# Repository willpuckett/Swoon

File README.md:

# Swoon Half Xiao'd

> Yet another diode matrix rework of the
> [Ferris Sweep Half Swept](https://github.com/davidphilipbarr/Sweep/tree/main/Sweep%20half-swept)
> for
> [Seeed Xiao nRF52840](https://www.seeedstudio.com/Seeed-XIAO-BLE-nRF52840-p-5201.html).

## Motivations

- Utilise Seeed Xiao—it's cuter
- Experiment with parts consignment for PCBA of hotswaps
- Choose a battery that can be easily changed by users who do not solder
  (LIR1254)
- Explore using CI/CD for board variants, case, and top plate generation
- Locate each half's components on its respective top side for more affordable
  assembly and lower overall height

> [!NOTE]
> In a Hurry? Here are the relevant links for download. No need scroll...
>
> Boards [[flip](/jlcpcb/swoon_FLIP.zip)] [[left](/jlcpcb/swoon_LEFT.zip)]
> [[right](/jlcpcb/swoon_RIGHT.zip)] [[both](/jlcpcb/swoon_BOTH.zip)]
>
> Case
> [[step](https://nightly.link/willpuckett/Swoon/actions/runs/10987780383/Case_STEP.zip)]
> [[stl](https://nightly.link/willpuckett/Swoon/actions/runs/10987780383/Case_STL.zip)]
>
> Firmware
> [[latest ZMK Builds](https://nightly.link/willpuckett/Swoon/workflows/zmk/main/swoon.zip)]

## Variants

[^1]

### **Flip**

> [!IMPORTANT]
> You'll need to solder the upward facing jumpers on each half under the Xiao
> before use.

A flippable variant [[flip](/jlcpcb/swoon_FLIP.zip)] for hand-soldering, like
the original half-swept. **Flip** is also the most cost conscious variant—about
$7.60 to get 5 of the boards produced, enough for 2 full keyboads and a nice...
coaster?

> [!CAUTION]
> Use 3.7v LIR1254 (lithium ion rechargable) battery **only**.

#### BOM

|      QTY      |                   Part                    | JLCPCB Part # |
| :-----------: | :---------------------------------------: | :-----------: |
|       2       |          0906-2-15-20-75-14-11-0          |   C5261048    |
|       2       |            BAT-SMD_MY-LR44-02             |   C2902345    |
|       4       | 310-13-107-41-001000 or MF254V-11-07-0743 |   C5504401    |
| 68 (optional) |          3305-0-15-80-47-27-10-0          |   C17370797   |
|       2       |               MST22D18G2125               |   C2906280    |
|      34       | CD4148WS (or 1N4148 SOD-323 from Amazon)  |   C38587762   |
|      34       |      Your ChocV1 switches of choice       |      N/A      |
|       2       |         3.7V LIR1254 (NOT LR44!)          |      N/A      |

### **Left** and **Right**

These variants are designed to be produced and assembled by JLCPCB. Each zip
file [[left](/jlcpcb/swoon_LEFT.zip)] [[right](/jlcpcb/swoon_RIGHT.zip)] has the
a gerbers/drill zip, a cpl, and bom file. They should be fully assemblable, but
you'll need to preorder the parts through global sourcing before paying. The
3305s aren't cheap and they cost extra to assemble.

Each half is pre-jumpered in the gerbers so you can print and go.

> [!CAUTION]
> Use 3.7v LIR1254 (lithium ion rechargable) battery **only**.

There's also a [[both](/jlcpcb/swoon_BOTH.zip)] that will probably supersede the
**left** and **right** since it's cheaper to produce as a single piece.

## Case

There's a case
[[step](https://nightly.link/willpuckett/Swoon/actions/runs/10987780383/Case_STEP.zip)]
[[stl](https://nightly.link/willpuckett/Swoon/actions/runs/10987780383/Case_STL.zip)]
that's really more of a skin. Print and place the pcb directly in it.

> [!TIP]
> Polymaker TPU works well. It seems to like to print slow and cool—leave the
> door open.

TPU is relatively non-slip, and it absorbs and distributes the force of typing
very nicely, so no bumpons needed which further reduces height.

## Layouts

Download the
[latest ZMK Builds](https://nightly.link/willpuckett/Swoon/workflows/zmk/main/swoon.zip).
The link contains the following layouts...

### QWERTY

### Engram

### Engrammer

[^1]: This project is mostly setup for production and assembly variants in
    GitHub actions. ~~Production variants are newer to KiCad and there's still a
    few kinks, but hopefully they'll be worked out soon.~~ The KiBot team has
    resolved the issues this project will pull them in for a release shortly. In
    the mean time, use the files in the [jlcpcb](/jlcpcb/) directory.

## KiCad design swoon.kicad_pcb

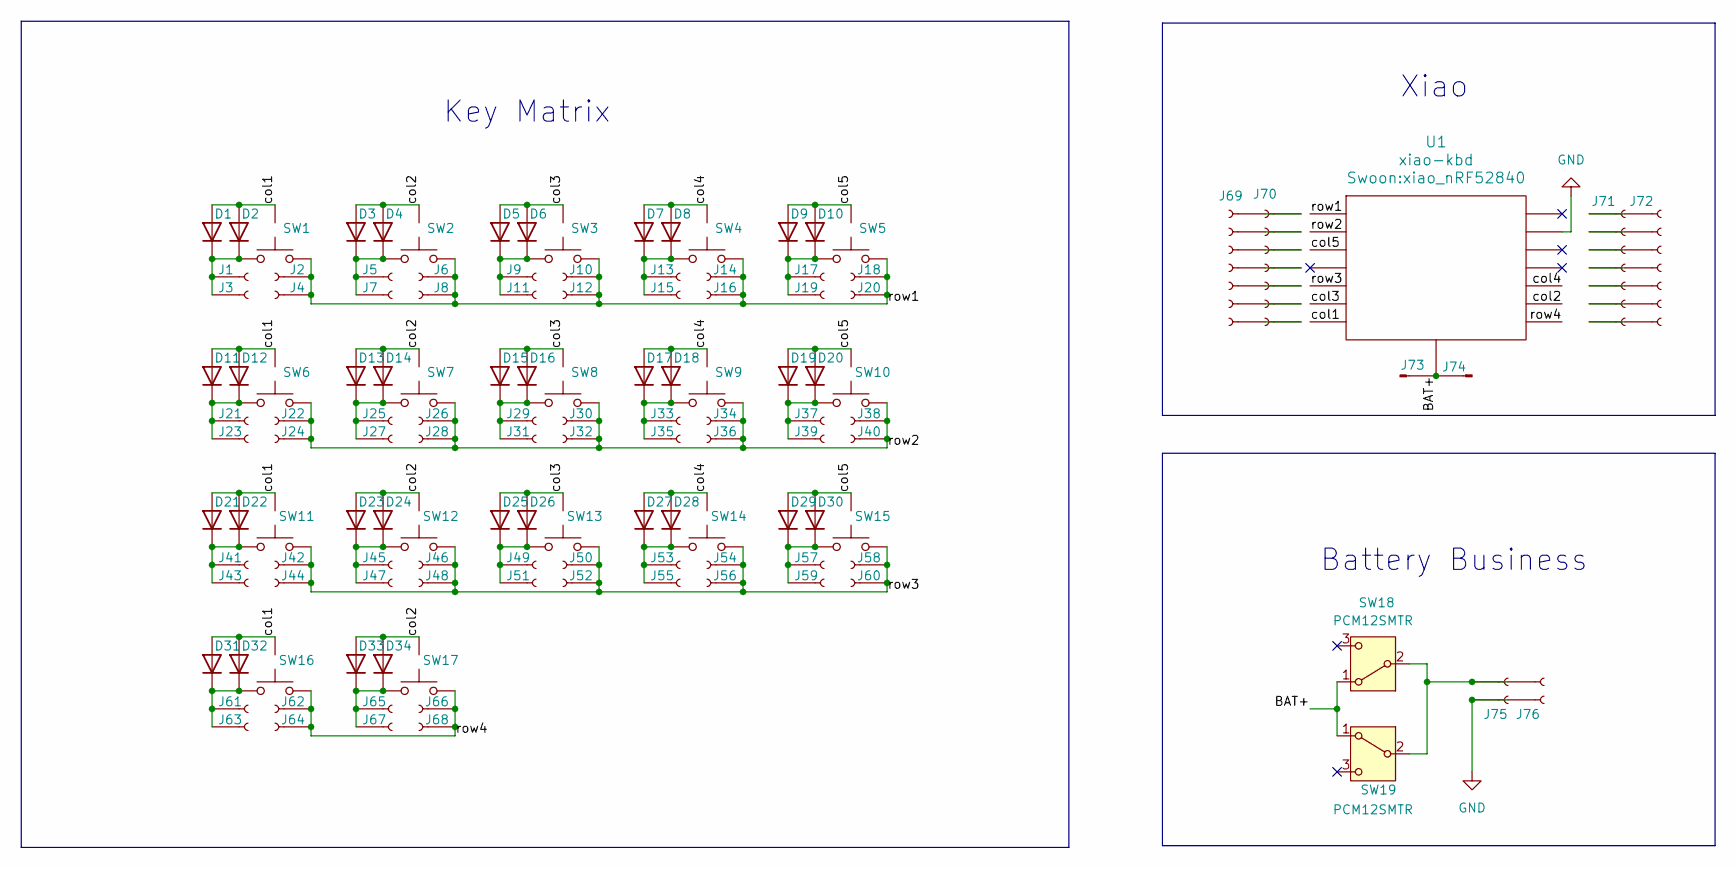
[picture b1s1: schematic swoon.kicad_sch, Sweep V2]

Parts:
D1, D2, D3, D4, D5, D6, D7, D8, D9, D10, D11, D12, D13, D14, D15, D16, D17, D18, D19, D20, D21, D22, D23, D24, D25, D26, D27, D28, D29, D30, D31, D32, D33, D34: CD4148WSP-C109001; D_0805_2012Metric
J1, J2, J3, J4, J5, J6, J7, J8, J9, J10, J11, J12, J13, J14, J15, J16, J17, J18, J19, J20, J21, J22, J23, J24, J25, J26, J27, J28, J29, J30, J31, J32, J33, J34, J35, J36, J37, J38, J39, J40, J41, J42, J43, J44, J45, J46, J47, J48, J49, J50, J51, J52, J53, J54, J55, J56, J57, J58, J59, J60, J61, J62, J63, J64, J65, J66, J67, J68: 3305-0-15-80-47-27-10-0
J69, J70, J71, J72: MF254V-11-07-0743
J73, J74: Mill Max 0906-2-15-20-75-14-11-0; 0906-2-15-20-75-14-11-0
J75, J76: JST SM02B-SRSS-TB(LF)(SN); JST_SH_SM02B-SRSS-TB_1x02-1MP_P1.00mm_Horizontal
SW1, SW2, SW3, SW4, SW5, SW6, SW7, SW8, SW9, SW10, SW11, SW12, SW13, SW14, SW15, SW16, SW17: SW_Push; SW_PG1350_vias
SW18, SW19: PCM12SMTR; SW_PCM12SMTR
U1: xiao-kbd; xiao_nRF52840

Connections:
/BAT+: J73.1, J74.1, SW18.1 (A), SW19.1 (A), U1.15 (BAT+)
/col1: D1.2 (A), D2.2 (A), D11.2 (A), D12.2 (A), D21.2 (A), D22.2 (A), D31.2 (A), D32.2 (A), SW1.3, SW6.3, SW11.3, SW16.3, U1.7 (D6)
/col2: D3.2 (A), D4.2 (A), D13.2 (A), D14.2 (A), D23.2 (A), D24.2 (A), D33.2 (A), D34.2 (A), SW2.3, SW7.3, SW12.3, SW17.3, U1.9 (D8)
/col3: D5.2 (A), D6.2 (A), D15.2 (A), D16.2 (A), D25.2 (A), D26.2 (A), SW3.3, SW8.3, SW13.3, U1.6 (D5)
/col4: D7.2 (A), D8.2 (A), D17.2 (A), D18.2 (A), D27.2 (A), D28.2 (A), SW4.3, SW9.3, SW14.3, U1.10 (D9)
/col5: D9.2 (A), D10.2 (A), D19.2 (A), D20.2 (A), D29.2 (A), D30.2 (A), SW5.3, SW10.3, SW15.3, U1.3 (D2)
/row1: J2.1, J4.1, J6.1, J8.1, J10.1, J12.1, J14.1, J16.1, J18.1, J20.1, SW1.1, SW2.1, SW3.1, SW4.1, SW5.1, U1.1 (D0)
/row2: J22.1, J24.1, J26.1, J28.1, J30.1, J32.1, J34.1, J36.1, J38.1, J40.1, SW6.1, SW7.1, SW8.1, SW9.1, SW10.1, U1.2 (D1)
/row3: J42.1, J44.1, J46.1, J48.1, J50.1, J52.1, J54.1, J56.1, J58.1, J60.1, SW11.1, SW12.1, SW13.1, SW14.1, SW15.1, U1.5 (D4)
/row4: J62.1, J64.1, J66.1, J68.1, SW16.1, SW17.1, U1.8 (D7)
GND: J75.1, J76.1, U1.13 (GND)
unnamed: D1.1 (K), D2.1 (K), J1.1, J3.1, SW1.2
unnamed: D3.1 (K), D4.1 (K), J5.1, J7.1, SW2.2
unnamed: D5.1 (K), D6.1 (K), J9.1, J11.1, SW3.2
unnamed: D7.1 (K), D8.1 (K), J13.1, J15.1, SW4.2
unnamed: D9.1 (K), D10.1 (K), J17.1, J19.1, SW5.2
unnamed: D11.1 (K), D12.1 (K), J21.1, J23.1, SW6.2
unnamed: D13.1 (K), D14.1 (K), J25.1, J27.1, SW7.2
unnamed: D15.1 (K), D16.1 (K), J29.1, J31.1, SW8.2
unnamed: D17.1 (K), D18.1 (K), J33.1, J35.1, SW9.2
unnamed: D19.1 (K), D20.1 (K), J37.1, J39.1, SW10.2
unnamed: D21.1 (K), D22.1 (K), J41.1, J43.1, SW11.2
unnamed: D23.1 (K), D24.1 (K), J45.1, J47.1, SW12.2
unnamed: D25.1 (K), D26.1 (K), J49.1, J51.1, SW13.2
unnamed: D27.1 (K), D28.1 (K), J53.1, J55.1, SW14.2
unnamed: D29.1 (K), D30.1 (K), J57.1, J59.1, SW15.2
unnamed: D31.1 (K), D32.1 (K), J61.1, J63.1, SW16.2
unnamed: D33.1 (K), D34.1 (K), J65.1, J67.1, SW17.2
unnamed: J69.1, J70.1
unnamed: J69.2, J70.2
unnamed: J69.3, J70.3
unnamed: J69.4, J70.4
unnamed: J69.5, J70.5
unnamed: J69.6, J70.6
unnamed: J69.7, J70.7
unnamed: J71.1, J72.1
unnamed: J71.2, J72.2
unnamed: J71.3, J72.3
unnamed: J71.4, J72.4
unnamed: J71.5, J72.5
unnamed: J71.6, J72.6
unnamed: J71.7, J72.7
unnamed: J75.2, J76.2, SW18.2 (B), SW19.2 (B)

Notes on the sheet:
Battery Business
Key Matrix
Xiao

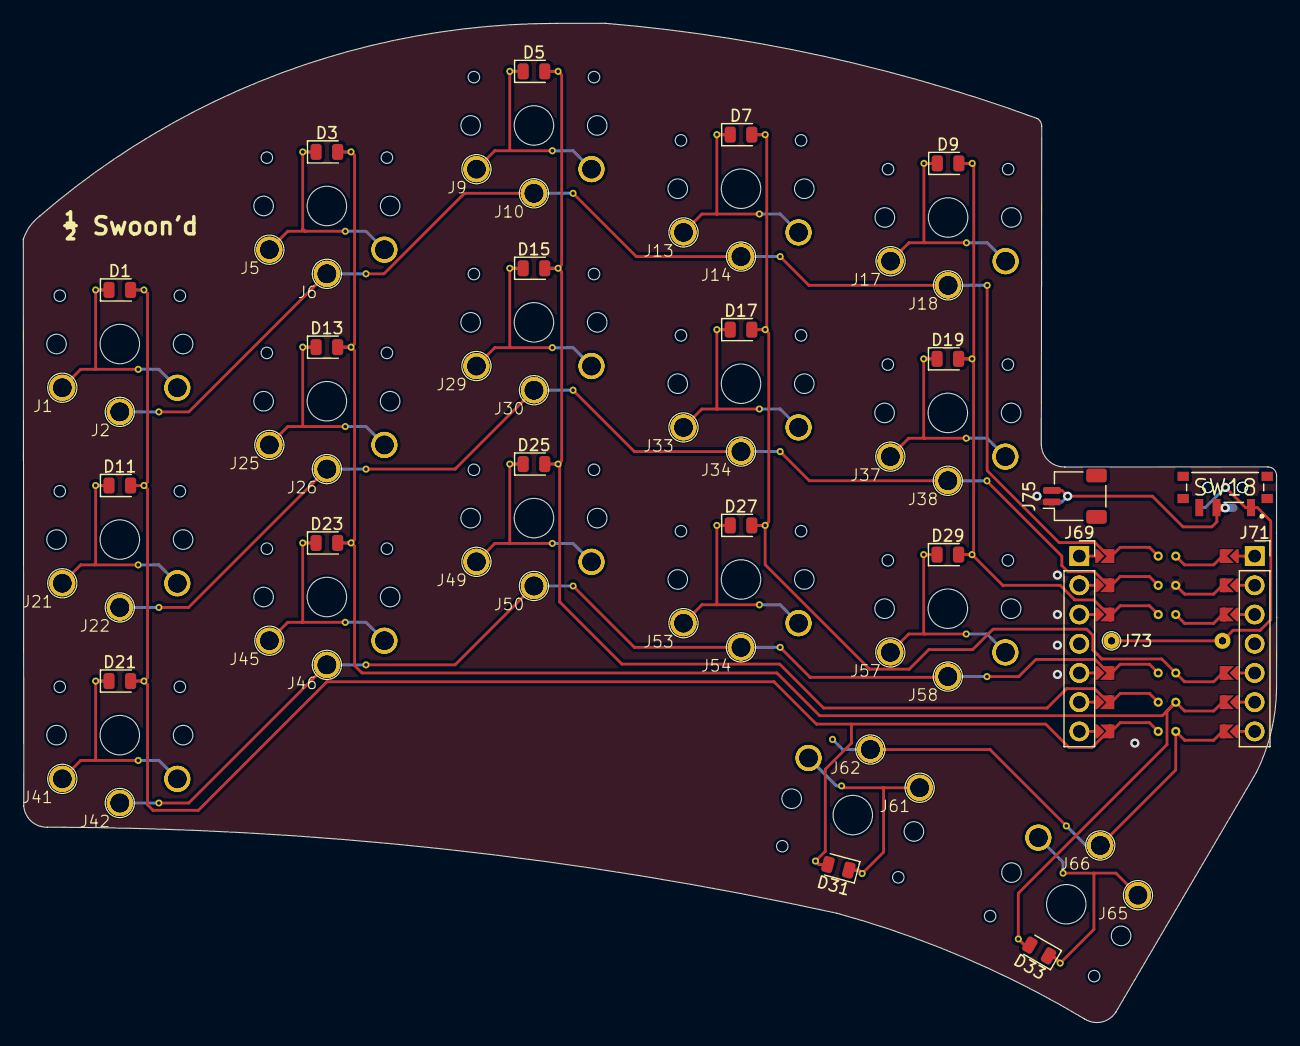
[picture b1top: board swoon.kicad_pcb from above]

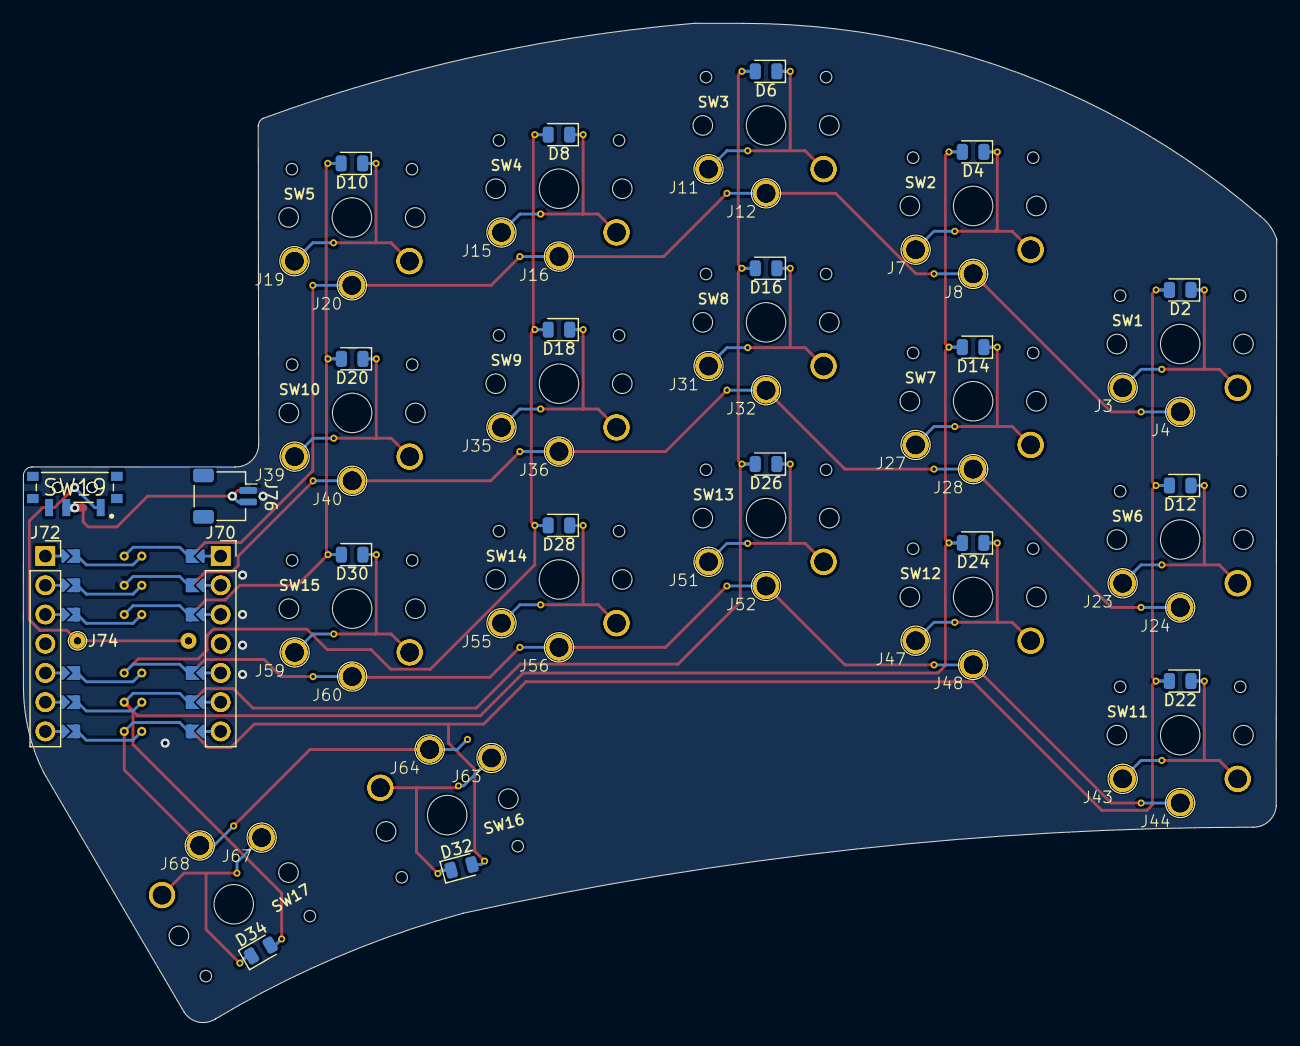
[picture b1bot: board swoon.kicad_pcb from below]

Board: 2 copper layers, 109.0 x 86.9 mm, 130 parts (56 on the bottom side), 43 nets.

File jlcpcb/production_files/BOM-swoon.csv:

Comment,Designator,Footprint,LCSC
CD4148WSP-C109001,"D1,D10,D11,D12,D13,D14,D15,D16,D17,D18,D19,D2,D20,D21,D22,D23,D24,D25,D26,D27,D28,D29,D3,D30,D31,D32,D33,D34,D4,D5,D6,D7,D8,D9",D_0805_2012Metric,C109001
JST SM02B-SRSS-TB(LF)(SN),"J75,J76",JST_SH_SM02B-SRSS-TB_1x02-1MP_P1.00mm_Horizontal,C160402
3305-0-15-80-47-27-10-0,"J1,J10,J11,J12,J13,J14,J15,J16,J17,J18,J19,J2,J20,J21,J22,J23,J24,J25,J26,J27,J28,J29,J3,J30,J31,J32,J33,J34,J35,J36,J37,J38,J39,J4,J40,J41,J42,J43,J44,J45,J46,J47,J48,J49,J5,J50,J51,J52,J53,J54,J55,J56,J57,J58,J59,J6,J60,J61,J62,J63,J64,J65,J66,J67,J68,J7,J8,J9",3305-0-15-80-47-27-10-0,C17370797
PCM12SMTR,"POWER_SW1,POWER_SW2",SW_PCM12SMTR,C221841
MF254V-11-07-0743,"J69,J70,J71,J72",MF254V-11-07-0743,C2889988
Mill Max 0906-2-15-20-75-14-11-0,"J73,J74",0906-2-15-20-75-14-11-0,C5261048

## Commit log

2024-08-20 position battery terminal & power switch
2024-08-21 add 0900-2-15-20-75-14-11-0
2024-08-21 add tenting puck, copper graphic
2024-08-21 add title text
2024-08-21 setup zmk
2024-08-21 correct dtsi
2024-08-21 correct typo
2024-08-21 fix modifiers
2024-08-21 add semi
2024-08-21 update production files
2024-08-21 change artifact naming schema
2024-09-06 add kicad action
2024-09-06 add kibot file
2024-09-06 update zmk action
2024-09-07 fix erc/drc kibot workflow
2024-09-07 try getting checks to run
2024-09-07 try again
2024-09-07 add some kibot stuff
2024-09-07 again
2024-09-07 correct dict
2024-09-07 add variants
2024-09-07 run without drc for testing
2024-09-07 update variant name
2024-09-07 add variants to kibot.yaml
2024-09-07 try changing capitalization
2024-09-08 add rotataed variant
2024-09-08 add mpn field
2024-09-08 trying DRC again
2024-09-08 fix mp errors
2024-09-09 add devcontainer
2024-09-09 getting jobs working
2024-09-09 organize devcontainer
2024-09-09 fix testpads, update kibot.yaml
2024-09-09 fix action
2024-09-09 change output to from_output type
2024-09-09 fix indentation
2024-09-09 correcting archive output
2024-09-10 add cadquery container
2024-09-12 place origins for svg
2024-09-12 add case action
2024-09-13 reorganize library files
2024-09-13 erroring var_rename stuff
2024-09-13 correct variant capitalization, add all variants
2024-09-20 fix 3d models
2024-09-20 correct compress jobs in kibot.yaml
2024-09-20 using drill files from flip in left and right variants
2024-09-20 remove commas from targets list
2024-09-20 correct edge cuts and schematic globs
2024-09-20 change board outline and archive names
2024-09-20 update pcb
2024-09-20 clean up
2024-09-21 more working with v2_dk8
2024-09-22 add zips of Flip, Left, and Right variants
2024-09-22 correct image
2024-09-22 add tip, cautions
2024-09-22 add more pull quotes
2024-09-22 correct 3305 count
2024-09-23 add keymap drawer
2024-09-23 add build123d workflow
2024-09-23 Revert "add build123d workflow"
    This reverts commit e4690586cedccb0c1d963ceafc7b9e119b231d94.
2024-09-23 refine actions
2024-09-23 test case action without artifact
2024-09-23 correct script location
2024-09-23 evolve case.yml
2024-09-23 zudgeing case
2024-09-23 touch up a few corners
2024-09-23 reroute switches
2024-09-23 cover vias
2024-10-08 reorganize zmk config directory
2025-11-01 fix missing .images folder
2025-11-01 fix badge
2025-11-01 fix keymap links
